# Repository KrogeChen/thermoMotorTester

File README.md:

# thermoMotorTester

热马达综合测试仪

## 功能介绍

- 测试热马达的行程、温度、负载力、功率、电压、电流
- 系统电压DC12-24V
- 测试电压AC12、AC24V、AC36V、AC110、AC220V
- 需要配置PC端软件，记录参数的曲线
- 能够长期运行对产品进行老化

## 系统组成 

- 主控板、继电器输出板、测力仪、电参数测量仪、温控仪、变压器、PC软件

## 器件选型

* [MCU:STM32F103RCT6](https://github.com/KrogeChen/thermoMotorTester/tree/master/document/STM32F103) 
* [继电器:HF115-005-2ZS](https://github.com/KrogeChen/thermoMotorTester/tree/master/document/HF115F_005-2ZS4AF) 
* [电参:PM9808](https://github.com/KrogeChen/thermoMotorTester/tree/master/document/PM9808) 
* [温控仪:LU-926M](https://github.com/KrogeChen/thermoMotorTester/tree/master/document/LU_926M) 

## 设计说明

- 设备电压:AC220V 
- 主板实现电压的转换、测量数据的采集
- 测试电压输出采用继电器触点互锁的方式、任何时候只允许输出一组电压。
- 设计7个输入点、7个输出点
- 5组UART通讯(2组RS323、1组RS485、1组TTL、1组BGH)
- 主要协议modbus RTU 主机，bough

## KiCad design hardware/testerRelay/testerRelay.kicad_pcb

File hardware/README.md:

# 硬件目录
硬件Kicad库(https://github.com/KrogeChen/kicadLib)

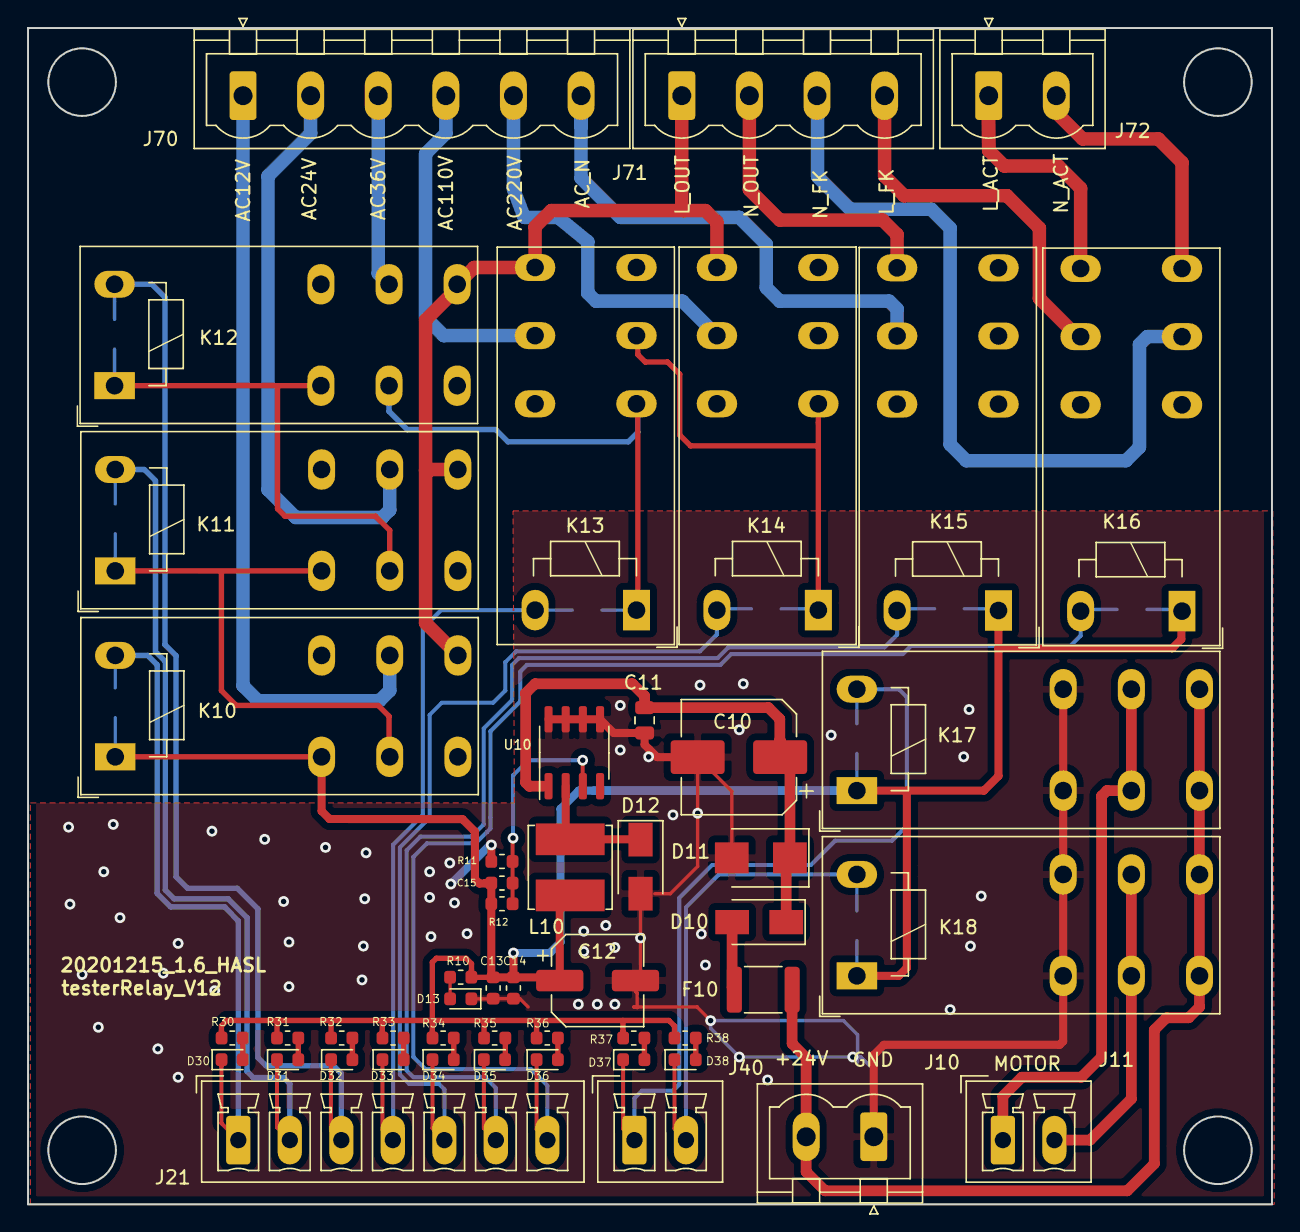
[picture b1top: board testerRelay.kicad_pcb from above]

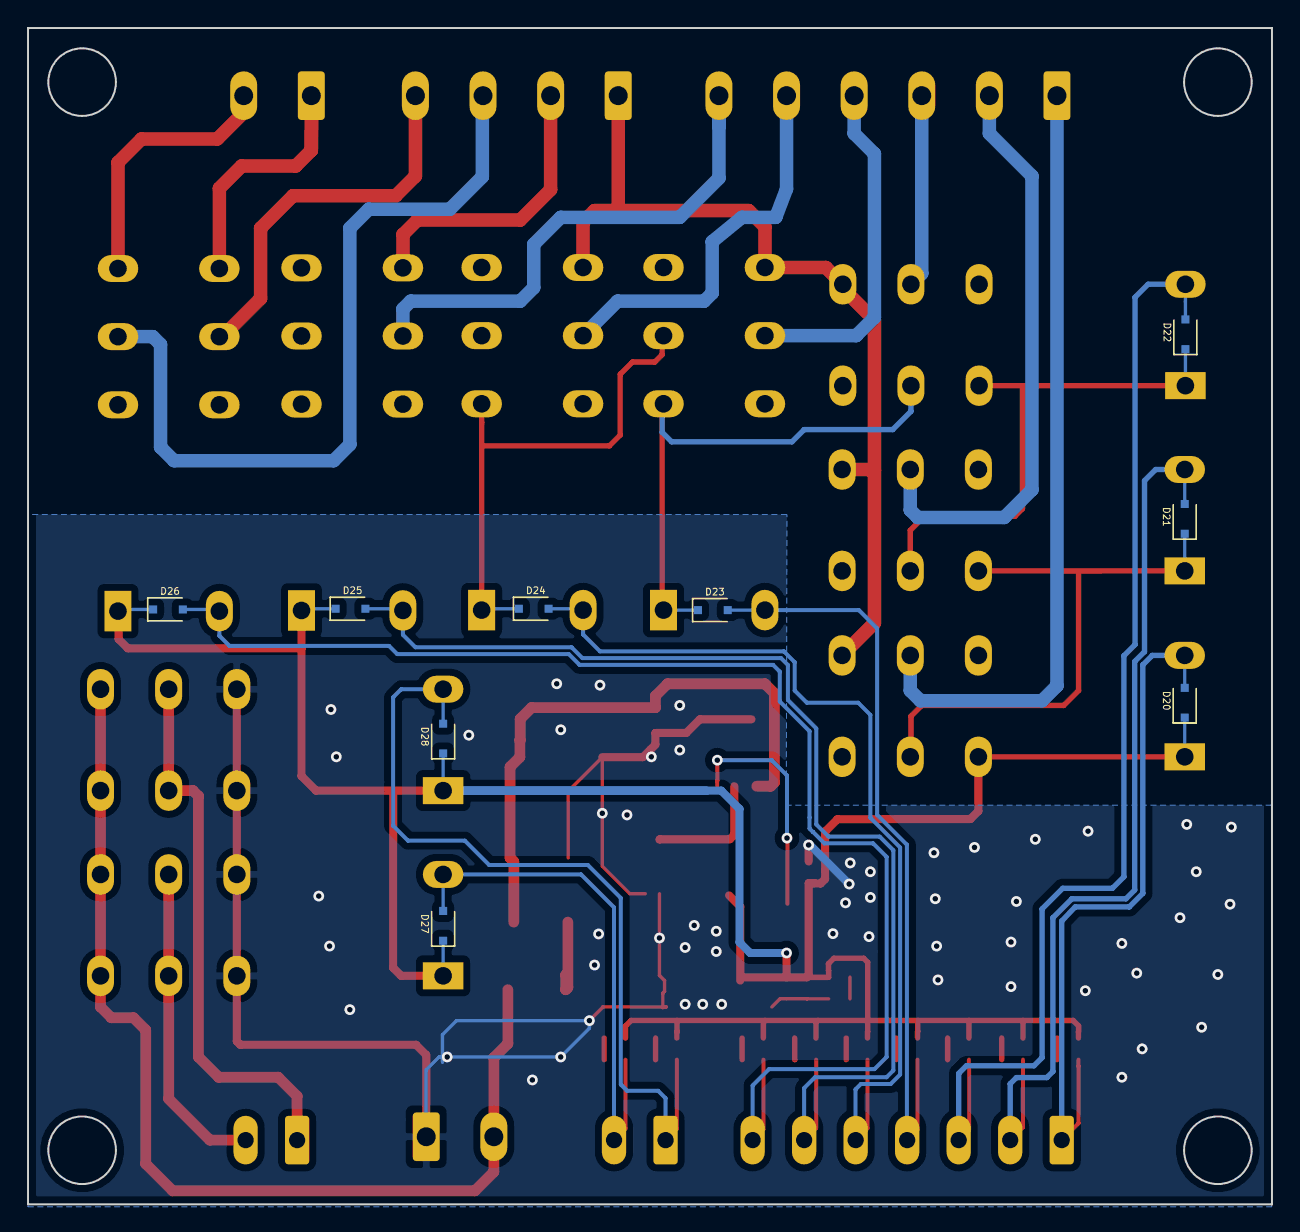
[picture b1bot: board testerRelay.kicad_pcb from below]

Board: 2 copper layers, 92.0 x 87.0 mm, 59 parts (9 on the bottom side), 44 nets.

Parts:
C10: 47uF; CP_Elec_8x6.5
C11: 1uF; C_0805_2012Metric
C12: 220uF; CP_Elec_6.3x5.4
C13: 1uF; C_0603_1608Metric
C14: 100nF; C_0603_1608Metric
C15: 3.3nF; C_0603_1608Metric
D10, D12: SS14; D_SMA
D11: SMBJ28A; D_SMB
D13, D30, D31, D32, D33, D34, D35, D36, D37, D38: red; LED_0603_1608Metric
D20, D21, D22, D23, D24, D25, D26, D27, D28: 1N4148; D_SOD-323F
F10: 200mA; Fuse_1812_4532Metric
J10: Power; PhoenixContact_MSTBVA_2,5_2-G_1x02_P5.00mm_Vertical
J11: MOTOR; PhoenixContact_MCV_1,5_2-G-3.81_1x02_P3.81mm_Vertical
J21: CK; PhoenixContact_MCV_1,5_7-G-3.81_1x07_P3.81mm_Vertical
J40: CK; PhoenixContact_MCV_1,5_2-G-3.81_1x02_P3.81mm_Vertical
J70: transformer; PhoenixContact_MSTBVA_2,5_6-G_1x06_P5.00mm_Vertical
J71: PM9808_L; PhoenixContact_MSTBVA_2,5_4-G_1x04_P5.00mm_Vertical
J72: actuator; PhoenixContact_MSTBVA_2,5_2-G_1x02_P5.00mm_Vertical
K10, K11, K12, K13, K14, K15, K16, K17, K18: HF115-005-2ZS4; Relay_DPDT_Schrack-RT2-FormC_RM5mm
L10: 68uH; L_Bourns_SRN6045TA
R10, R30, R31, R32, R33, R34, R35, R36, R37, R38: 4.7k; R_0603_1608Metric
R11: 1k; R_0603_1608Metric
R12: 3.6k; R_0603_1608Metric
U10: XL1509; SOIC-8_3.9x4.9mm_P1.27mm

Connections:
+5VD: C12.1, C13.1, C14.1, C15.1, D20.1, D25.1, D26.1, D27.1, D28.1, K10.12, K10.A1, K15.A1, K16.A1, K17.A1, K18.A1, L10.2, R10.2, R12.2, R30.1, R31.1, R32.1, R33.1, R34.1, R35.1, R36.1, R37.1, R38.1
/AC12V: J70.1, K10.21
/AC24V: J70.2, K11.21
/AC36V: J70.3, K12.21
/AC110V: J70.4, K13.21
/AC220V: J70.5, K14.21
/AC_N: J70.6, K15.21
/CK0: D20.2, D30.1, J21.1, K10.A2
/CK1: D21.2, D31.1, J21.2, K11.A2
/CK2: D22.2, D32.1, J21.3, K12.A2
/CK3: D23.2, D33.1, J21.4, K13.A2
/CK4: D24.2, D34.1, J21.5, K14.A2
/CK5: D25.2, D35.1, J21.6, K15.A2
/CK6: D26.2, D36.1, J21.7, K16.A2
/CK7: D28.2, D37.1, J40.1, K17.A2
/CK8: D27.2, D38.1, J40.2, K18.A2
/K11CV: D21.1, K10.11, K11.12, K11.A1
/K12CV: D22.1, K11.11, K12.12, K12.A1
/K13CV: D23.1, K12.11, K13.12, K13.A1
/K14CV: D24.1, K13.11, K14.12, K14.A1
/L_ACT: J72.1, K16.24
/L_FK: J71.4, K16.21
/L_OUT: J71.1, K10.24, K11.24, K12.24, K13.24, K14.24
/M_1: J11.2, K18.11, K18.21
/M_2: J11.1, K17.11, K17.21
/N_ACT: J72.2, K16.14
/N_FK: J71.3, K16.11
/N_OUT: J71.2, K15.24
/VIN: F10.1, J10.2, K17.14, K17.24, K18.14, K18.24
GND: C10.2, C11.2, C12.2, C13.2, C14.2, D11.2, D12.2, D13.1, J10.1, K17.12, K17.22, K18.12, K18.22, R11.2, U10.5, U10.6, U10.7, U10.8
unnamed: C15.2, R11.1, R12.1, U10.3
unnamed: D10.2, F10.2
unnamed: D12.1, L10.1, U10.2
unnamed: D13.2, R10.1
unnamed: D30.2, R30.2
unnamed: D31.2, R31.2
unnamed: D32.2, R32.2
unnamed: D33.2, R33.2
unnamed: D34.2, R34.2
unnamed: D35.2, R35.2
unnamed: D36.2, R36.2
unnamed: D37.2, R37.2
unnamed: D38.2, R38.2
VDD: C10.1, C11.1, D10.1, D11.1, U10.1

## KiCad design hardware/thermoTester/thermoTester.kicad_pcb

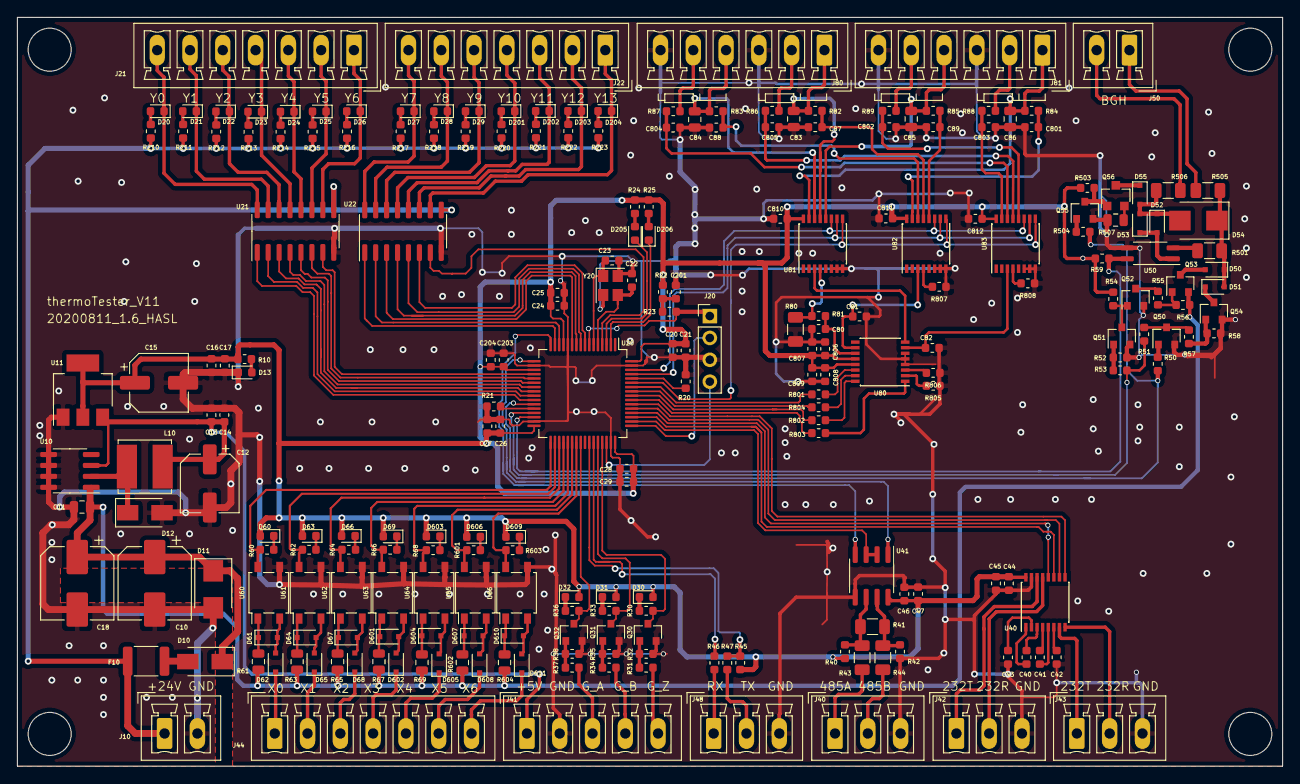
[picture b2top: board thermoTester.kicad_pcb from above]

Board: 2 copper layers, 147.0 x 87.0 mm, 233 parts (0 on the bottom side), 192 nets.

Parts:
C10, C18: 47uF; CP_Elec_8x6.5
C11: 1uF; C_0805_2012Metric
C12, C15: 220uF; CP_Elec_6.3x5.4
C13, C16, C20, C25, C26, C29, C44, C47, C204, C807, C808: 1uF; C_0603_1608Metric
C14, C17, C21, C24, C27, C28, C40, C41, C42, C43, C45, C46, C201, C203, C806, C809, C810, C811, C812: 100nF; C_0603_1608Metric
C22, C23: 20pF; C_0603_1608Metric
C80, C81, C82, C87, C88, C89, C801, C802, C803, C804, C805: 47nF; C_0603_1608Metric
C83, C84, C85, C86: 100nF; C_0805_2012Metric
D10, D12: SS14; D_SMA
D11: SMBJ28A; D_SMB
D13, D205, D206: Red; LED_0603_1608Metric
D20, D21, D22, D23, D24, D25, D26, D27, D28, D29, D30, D31, D32, D60, D63, D66, D69, D201, D202, D203, D204, D603, D606, D609: Red; D_0603_1608Metric
D50, D51, D52, D53, D55, D61, D62, D64, D65, D67, D68, D601, D602, D604, D605, D607, D608, D610, D611: 1N4148; D_SOD-323F
D54: SMBJ28CA; D_SMB
F10: 200mA; Fuse_1812_4532Metric
J10: Power; PhoenixContact_MCV_1,5_2-G-3.81_1x02_P3.81mm_Vertical
J20: PRG; PinHeader_1x04_P2.54mm_Vertical
J21, J22: YOUT; PhoenixContact_MCV_1,5_7-G-3.81_1x07_P3.81mm_Vertical
J40: temperature; PhoenixContact_MCV_1,5_3-G-3.81_1x03_P3.81mm_Vertical
J41: grating; PhoenixContact_MCV_1,5_5-G-3.81_1x05_P3.81mm_Vertical
J42: load; PhoenixContact_MCV_1,5_3-G-3.81_1x03_P3.81mm_Vertical
J43: PM9808_TR; PhoenixContact_MCV_1,5_3-G-3.81_1x03_P3.81mm_Vertical
J44: XIN; PhoenixContact_MCV_1,5_7-G-3.81_1x07_P3.81mm_Vertical
J48: CPTTL; PhoenixContact_MCV_1,5_3-G-3.81_1x03_P3.81mm_Vertical
J50: bough; PhoenixContact_MCV_1,5_2-G-3.81_1x02_P3.81mm_Vertical
J80, J81: PT100; PhoenixContact_MCV_1,5_6-G-3.81_1x06_P3.81mm_Vertical
L10: 68uH; L_Bourns_SRN6045TA
Q30, Q31, Q32, Q50, Q51, Q52, Q54, Q55: BC817; SOT-23
Q53: BC807; SOT-23
Q56: AO3422; SOT-23_big
R10, R20, R21, R24, R25, R51, R57, R60, R62, R64, R66, R68, R601, R603: 2.7k; R_0603_1608Metric
R22, R52: 47k; R_0603_1608Metric
R23: 470; R_0603_1608Metric
R30, R31, R32, R33, R34, R35, R36, R37, R38, R40, R42, R45, R50, R54, R55, R56, R503, R504: 10k; R_0603_1608Metric
R41: NP_120; R_1206_3216Metric
R43, R44: 20; R_1206_3216Metric
R46, R47: 100; R_0603_1608Metric
R53, R58, R59: 5.1k; R_0603_1608Metric
R61, R63, R65, R67, R69, R602, R604: 7.5k; R_0805_2012Metric
R80: 100R; R_1206_3216Metric
R81, R82, R83, R84, R85, R86, R87, R88, R89: 4.7k; R_0603_1608Metric
R210, R211, R212, R213, R214, R215, R216, R217, R218, R219, R220, R221, R222, R223: 33k; R_0603_1608Metric
R501: 5.1k; R_1206_3216Metric
R505, R506: 20R; R_1206_3216Metric
R507: 1R; R_0805_2012Metric
R801, R802, R803, R804, R805, R806, R807, R808: 47R; R_0603_1608Metric
U10: XL1509; SOIC-8_3.9x4.9mm_P1.27mm
U11: LM1117-3.3; SOT-223
U20: M_STM32F103RCT6; LQFP-64_10x10mm_P0.5mm
U21, U22: ULN2003; SOIC-16_3.9x9.9mm_P1.27mm
U40: SP3232; SSOP-16_4.4x5.2mm_P0.65mm
U41: SP3485CN; SOIC-8_3.9x4.9mm_P1.27mm
U50: EL3H4B; SSOP-4_2.7x5.05mm_P1.27mm
U60, U61, U62, U63, U64, U65, U66: EL357N; SO-4_4.4x4.3mm_P2.54mm
U80: ADS1220IPWR; SSOP-16_4.4x5.2mm_P0.65mm
U81, U82, U83: CD4051B; SSOP-16_4.4x5.2mm_P0.65mm
Y20: 12M; Crystal_SMD_3225-4Pin_3.2x2.5mm

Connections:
+5VD: C12.1, C13.1, C14.1, J41.1, L10.2, U10.3, U11.3
/AIN0: C80.2, R81.1, U80.11
/AIN1: C81.1, U80.10, U82.3
/AIN2: C82.1, U80.7, U83.3
/BGH1: J50.1, R505.1
/BGH2: J50.2, R506.1
/CP_RX: J48.1, R46.2
/CP_TX: J48.2, R47.2
/DIN: R802.1, U20.56
/DOUT: R804.1, U20.57
/IDAC1: U80.8, U81.3
/LED0: D205.1, U20.3
/LED1: D206.1, U20.2
/MRX1: R46.1, U20.43
/MRX2: U20.17, U41.1
/MRX3: R59.1, U20.30, U50.4
/MRX4: U20.52, U40.12
/MRX5: U20.54, U40.9
/MTA: Q32.3, R36.2, U20.40
/MTB: Q31.3, R33.2, U20.44
/MTX1: R45.1, R47.1, U20.42
/MTX2: U20.16, U41.4
/MTX3: R51.1, R53.1, U20.29
/MTX4: U20.51, U40.11
/MTX5: U20.53, U40.10
/MTZ: Q30.3, R30.2, U20.45
/M_X0: R60.2, U20.33, U60.4
/M_X1: R62.2, U20.34, U61.4
/M_X2: R64.2, U20.35, U62.4
/M_X3: R66.2, U20.36, U63.4
/M_X4: R68.2, U20.37, U64.4
/M_X5: R601.2, U20.38, U65.4
/M_X6: R603.2, U20.39, U66.4
/M_Y0: U20.26, U21.1
/M_Y1: U20.25, U21.2
/M_Y2: U20.24, U21.3
/M_Y3: U20.23, U21.4
/M_Y4: U20.22, U21.5
/M_Y5: U20.21, U21.6
/M_Y6: U20.20, U21.7
/M_Y7: U20.15, U22.1
/M_Y8: U20.14, U22.2
/M_Y9: U20.11, U22.3
/M_Y10: U20.10, U22.4
/M_Y11: U20.9, U22.5
/M_Y12: U20.8, U22.6
/M_Y13: U20.4, U22.7
/NRST: J20.1, R23.2, U20.7
/OVLD: Q56.2, R507.1
/P0_L1: C83.2, J80.1, R82.2, U81.13
/P0_L2: J80.2, R86.2
/P1_L1: C84.2, J80.4, R83.2, U81.14
/P1_L2: J80.5, R87.2
/P2_L1: C86.1, J81.1, R84.2, U81.15
/P2_L2: J81.2, R88.1
/P3_L1: C85.1, J81.4, R85.2, U81.12
/P3_L2: J81.5, R89.2
/RDY: R801.1, U20.58
/RS1_A: J40.1, R43.1
/RS1_B: J40.2, R44.1
/RS2_R: J42.2, U40.13
/RS2_T: J42.1, U40.14
/RS3_R: J43.2, U40.8
/RS3_T: J43.1, U40.7
/SCLK: R803.1, U20.55
/SL0: U20.62, U81.11, U82.11, U83.11
/SL1: U20.61, U81.10, U82.10, U83.10
/SL2: U20.59, U81.9, U82.9, U83.9
/SWCLK: J20.2, U20.49
/SWDIO: J20.4, U20.46
/TRS: R50.2, R504.1, U20.27
/TR_S1: U20.50, U41.2, U41.3
/TTL_A: J41.3, R37.1
/TTL_B: J41.4, R34.1
/TTL_Z: J41.5, R31.1
/VIN: F10.1, J10.1, R210.2, R211.2, R212.2, R213.2, R214.2, R215.2, R216.2, R217.2, R218.2, R219.2, R220.2, R221.2, R222.2, R223.2, U21.9, U22.9
/X0: D62.1, J44.1
/X1: D65.1, J44.2
/X2: D68.1, J44.3
/X3: D602.1, J44.4
/X4: D605.1, J44.5
/X5: D608.1, J44.6
/X6: D611.1, J44.7
/Y0: D20.1, J21.7, U21.16
/Y1: D21.1, J21.6, U21.15
/Y2: D22.1, J21.5, U21.14
/Y3: D23.1, J21.4, U21.13
/Y4: D24.1, J21.3, U21.12
/Y5: D25.1, J21.2, U21.11
/Y6: D26.1, J21.1, U21.10
/Y7: D27.1, J22.7, U22.16
/Y8: D28.1, J22.6, U22.15
/Y9: D29.1, J22.5, U22.14
/Y10: D201.1, J22.4, U22.13
/Y11: D202.1, J22.3, U22.12
/Y12: D203.1, J22.2, U22.11
/Y13: D204.1, J22.1, U22.10
GND: C10.2, C11.2, C12.2, C13.2, C14.2, C15.2, C16.2, C17.2, C18.2, C20.1, C21.1, C22.2, C23.2, C24.1, C25.1, C26.2, C27.1, C28.1, C29.2, C42.2, C43.2, C44.2, C45.1, C46.2, C47.2, C80.1, C81.2, C82.2, C83.1, C84.1, C85.2, C86.2, C87.1, C88.1, C89.2, C201.2, C203.2, C204.2, C801.2, C802.2, C803.2, C804.2, C805.2, C806.1, C807.1, C808.2, C809.2, C810.2, C811.2, C812.2, D11.2, D12.2, D13.1, J10.2, J20.3, J40.3, J41.2, J42.3, J43.3, J48.3, J80.3, J80.6, J81.3, J81.6, Q30.2, Q31.2, Q32.2, Q50.2, Q51.2, Q52.2, Q54.2, Q55.2, R20.2, R21.1, R32.2, R35.2, R38.2, R42.1, R52.2, R58.2, R80.2, R507.2, R805.1, R806.1, R807.1, R808.1, U10.5, U10.6, U10.7, U10.8, U11.1, U20.12, U20.18, U20.31, U20.47, U20.63, U21.8, U22.8, U40.15, U41.5, U50.3, U60.3, U61.3, U62.3, U63.3, U64.3, U65.3, U66.3, U80.4, U80.5, U80.6, U81.6, U81.7, U81.8, U82.6, U82.7, U82.8, U83.6, U83.7, U83.8, Y20.2, Y20.4
unnamed: C22.1, U20.5, Y20.3
unnamed: C23.1, U20.6, Y20.1
unnamed: C40.1, U40.1
unnamed: C40.2, U40.3
unnamed: C41.1, U40.4
unnamed: C41.2, U40.5
unnamed: C42.1, U40.6
unnamed: C43.1, U40.2
unnamed: C87.2, R82.1, U82.13
unnamed: C88.2, R83.1, U82.14
unnamed: C89.1, R85.1, U82.12
unnamed: C201.1, R22.2, R23.1
unnamed: C801.1, R84.1, U82.15
unnamed: C802.1, R89.1, U83.12
unnamed: C803.1, R88.2, U83.15
unnamed: C804.1, R87.1, U83.14
unnamed: C805.1, R86.1, U83.13
unnamed: D10.2, F10.2
unnamed: D12.1, L10.1, U10.2
unnamed: D13.2, R10.1
unnamed: D20.2, R210.1
unnamed: D21.2, R211.1
unnamed: D22.2, R212.1
unnamed: D23.2, R213.1
unnamed: D24.2, R214.1
unnamed: D25.2, R215.1
unnamed: D26.2, R216.1
unnamed: D27.2, R217.1
unnamed: D28.2, R218.1
unnamed: D29.2, R219.1
unnamed: D30.1, R30.1
unnamed: D31.1, R33.1
unnamed: D32.1, R36.1
unnamed: D50.1, D51.2, D54.1, R501.2, R505.2
unnamed: D50.2, Q53.3
unnamed: D51.1, Q54.3
unnamed: D52.1, D53.2, D54.2, D55.2, R506.2
unnamed: D52.2, D53.1, U50.1
unnamed: D55.1, Q56.3
unnamed: D60.1, R60.1
unnamed: D61.1, R61.1, U60.1
unnamed: D61.2, D62.2, U60.2
unnamed: D63.1, R62.1
unnamed: D64.1, R63.1, U61.1
unnamed: D64.2, D65.2, U61.2
unnamed: D66.1, R64.1
unnamed: D67.1, R65.1, U62.1
unnamed: D67.2, D68.2, U62.2
unnamed: D69.1, R66.1
unnamed: D201.2, R220.1
unnamed: D202.2, R221.1
unnamed: D203.2, R222.1
unnamed: D204.2, R223.1
unnamed: D205.2, R24.2
unnamed: D206.2, R25.2
unnamed: D601.1, R67.1, U63.1
unnamed: D601.2, D602.2, U63.2
unnamed: D603.1, R68.1
unnamed: D604.1, R69.1, U64.1
unnamed: D604.2, D605.2, U64.2
unnamed: D606.1, R601.1
unnamed: D607.1, R602.1, U65.1
unnamed: D607.2, D608.2, U65.2
unnamed: D609.1, R603.1
unnamed: D610.1, R604.1, U66.1
unnamed: D610.2, D611.2, U66.2
unnamed: Q30.1, R31.2, R32.1
unnamed: Q31.1, R34.2, R35.1
unnamed: Q32.1, R37.2, R38.1
unnamed: Q50.1, R50.1
unnamed: Q50.3, R51.2, R57.1
unnamed: Q51.1, R52.1, R53.2
unnamed: Q51.3, Q52.1, R54.1
unnamed: Q52.3, R55.2
unnamed: Q53.1, R55.1, R56.2
unnamed: Q54.1, R57.2, R58.1
unnamed: Q55.1, R504.2
unnamed: Q55.3, Q56.1, R503.2
unnamed: R20.1, U20.60
unnamed: R21.2, U20.28
unnamed: R40.1, R41.2, R43.2, U41.6
unnamed: R41.1, R42.2, R44.2, U41.7
unnamed: R80.1, R81.2, U81.4
unnamed: R501.1, U50.2
unnamed: R801.2, U80.14
unnamed: R802.2, U80.16
unnamed: R803.2, U80.1
unnamed: R804.2, U80.15
unnamed: R805.2, U80.2
unnamed: R806.2, U80.3
unnamed: R807.2, U82.4
unnamed: R808.2, U83.4
VCC: C15.1, C16.1, C17.1, C20.2, C21.2, C24.2, C25.2, C26.1, C27.2, C28.2, C29.1, C44.1, C45.2, C46.1, C47.1, C203.1, C204.1, C806.2, C807.2, C808.1, C809.1, C810.1, C811.1, C812.1, D30.2, D31.2, D32.2, D60.2, D63.2, D66.2, D69.2, D603.2, D606.2, D609.2, R10.2, R22.1, R24.1, R25.1, R40.2, R45.2, R54.2, R59.2, R503.1, U11.2, U11.4, U20.13, U20.19, U20.32, U20.48, U20.64, U40.16, U41.8, U80.12, U80.13, U81.16, U82.16, U83.16
VDD: C10.1, C11.1, C18.1, D10.1, D11.1, Q53.2, R56.1, R61.2, R63.2, R65.2, R67.2, R69.2, R602.2, R604.2, U10.1

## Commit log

2020-05-13 thermoMotor tester work is start
2020-05-21 hardware design is complete
2020-05-21 relay out pcb is design
2020-05-22 adjustment line direction
2020-05-28 创建目录的readme文件
2020-05-28 产品硬件目录增加readme
2020-05-29 add mcu datasheet and reference manual
2020-05-29 add docment url
2020-05-29 增加电参测量仪的通信资料
2020-05-29 modify folder name
2020-05-29 上传继电器datasheets
2020-05-29 modify url link address
2020-05-29 add temperature control
2020-05-31 Update README.md
    add kicad lib url
2020-06-08 增加触摸屏的开发资料
2020-06-13 add module
2020-06-13 frist add files
2020-06-15 system is run
2020-06-19 salve module 0x03 command is debug complete
2020-06-22 modbus可以较为稳定运行的版本
2020-06-24 修改模块，采用结构体数组的方式存储实例
2020-06-28 完善光栅模块，加入数字输入、输出模块
2020-06-29 增加触摸屏的工程文件
2020-07-08 初步版本调试通过
2020-07-11 提交一个待调试版本
2020-07-30 修改pcb文件，增加外壳支持
2020-08-05 Pcb manufactured in jlc
2020-08-10 V10硬件的代码，最后一个版本
2020-08-17 宏修改、完善
2020-08-17 按1.1版本修改硬件和软件代码
2020-08-20 加入modbus master 模块
2020-08-22 commit pt100
2020-08-24 统一sdt_true的定义值，0x01
2020-08-25 增加pt100分度表
2020-08-29 增加pt100温度计算程序
2020-09-26 增加连接极板文件
2020-09-28 分度表更新公式
2020-09-30 支持boot引导
2020-10-06 移入bough链路代码
2020-10-06 移入升级包的app代码
2020-10-10 upgrade 功能支持完毕
2020-10-10 存储模块支持数据变化再写入flash
2020-12-09 修正modbus 写部分的bug
2020-12-13 优化等级改为low，软件功能，初步通过
2020-12-15 增加曲线角度计算，pcb重新打样5pcs
2021-01-07 修正upgradefiles升级的块，超过8bits的问题
2024-08-14 加入隔热槽设计
2024-08-15 修改为沉金板
